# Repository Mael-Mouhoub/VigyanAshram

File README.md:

# VigyanAshram
Project realised by Mael Mouhoub for Vigyan Ashram 
you can contact me for any information : maelmt@hotmail.fr more information in my blog

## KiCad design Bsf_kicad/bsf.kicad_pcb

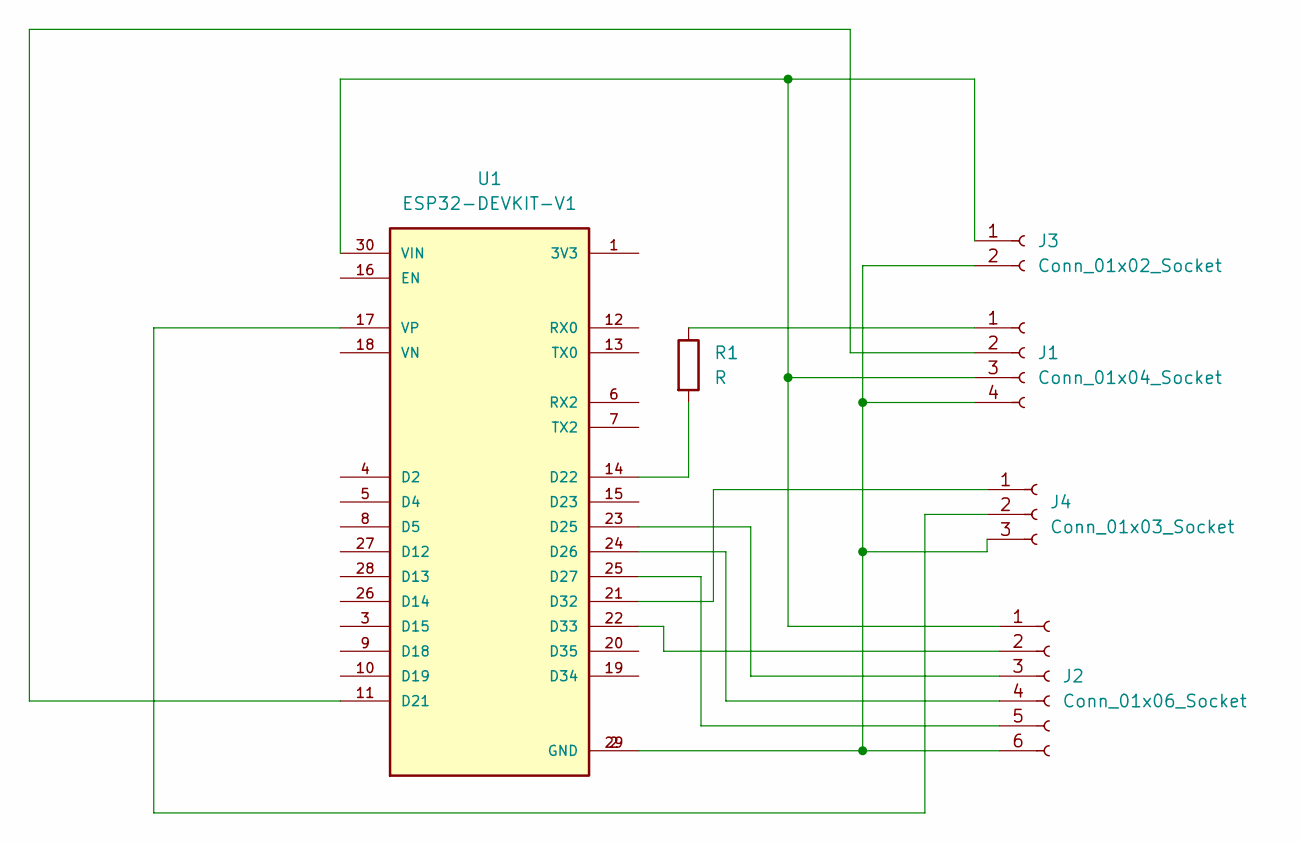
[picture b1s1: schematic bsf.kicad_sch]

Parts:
J1: Conn_01x04_Socket; PinSocket_1x04_P2.54mm_Vertical
J2: Conn_01x06_Socket; PinSocket_1x06_P2.54mm_Vertical
J3: Conn_01x02_Socket; PinSocket_1x02_P2.54mm_Vertical
J4: Conn_01x03_Socket; PinSocket_1x03_P2.54mm_Vertical
R1: R; R_0201_0603Metric_Pad0.64x0.40mm_HandSolder
U1: ESP32-DEVKIT-V1; DOIT-ESP32-MM; PARTREV N/A

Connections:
unnamed: J1.1, R1.1
unnamed: J1.2, U1.11 (D21)
unnamed: J1.3, J2.1, J3.1, U1.30 (VIN)
unnamed: J1.4, J2.6, J3.2, J4.3, U1.2 (GND), U1.29 (GND)
unnamed: J2.2, U1.22 (D33)
unnamed: J2.3, U1.23 (D25)
unnamed: J2.4, U1.24 (D26)
unnamed: J2.5, U1.25 (D27)
unnamed: J4.1, U1.21 (D32)
unnamed: J4.2, U1.17 (VP)
unnamed: R1.2, U1.14 (D22)

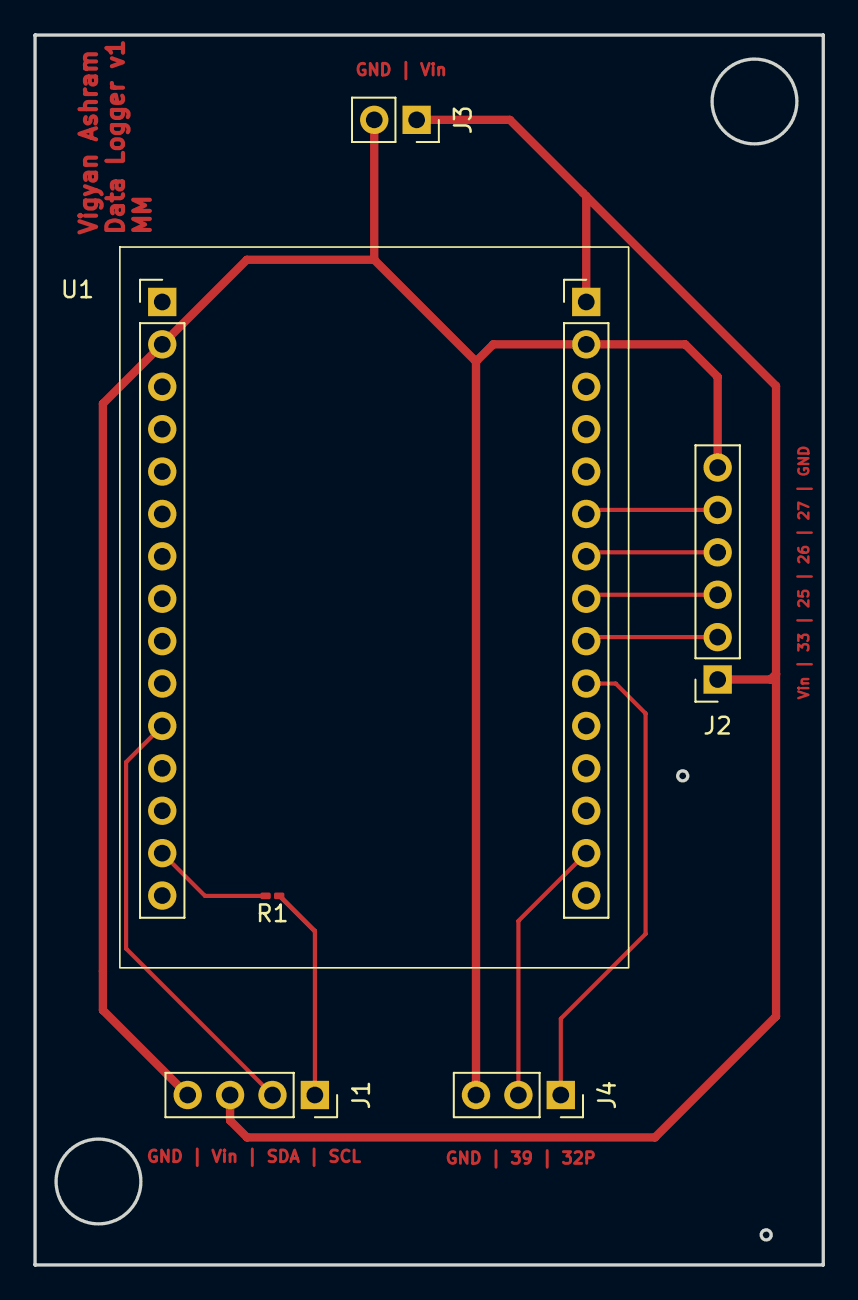
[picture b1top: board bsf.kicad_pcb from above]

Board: 2 copper layers, 47.2 x 73.7 mm, 6 parts (0 on the bottom side), 11 nets.
